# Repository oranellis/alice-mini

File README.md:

# OPA Alice Mini

Circuit from the OPA Alice design by DJJules, which itself was based on the Alice microphone by Scott Helmke, this is a PCB designed for a 3D printed mic enclosure for the JLI-2555B Capsule. I started the project off the back of the DIYPerks video where Matthew made a gorgeous mic based on the same capsule, however I wanted to connect it to my Scarlet Focusrite Solo instead and stumbled on the Alice mic. 

## Design

The circuit is identical to the OPA Alice preamp circuit with the exception of using MLCC's instead of Aluminium electrolytic capacitors. It is designed in Kicad 8 with the JLCPCB [plugin](https://github.com/Bouni/kicad-jlcpcb-tools), and ordered pre-assembled from JLCPCB. This is my first PCB design so please scrutinise it thoroughly before using or ordering one for yourself. **THE BOARD HAS NOT ARRIVED FOR ME YET AND MAY HAVE ISSUES**, please wait until I update this with the information of whether it works or not. If it does work, I will design the 3D printed enclosure and add those files here (or a link to the onshape page).

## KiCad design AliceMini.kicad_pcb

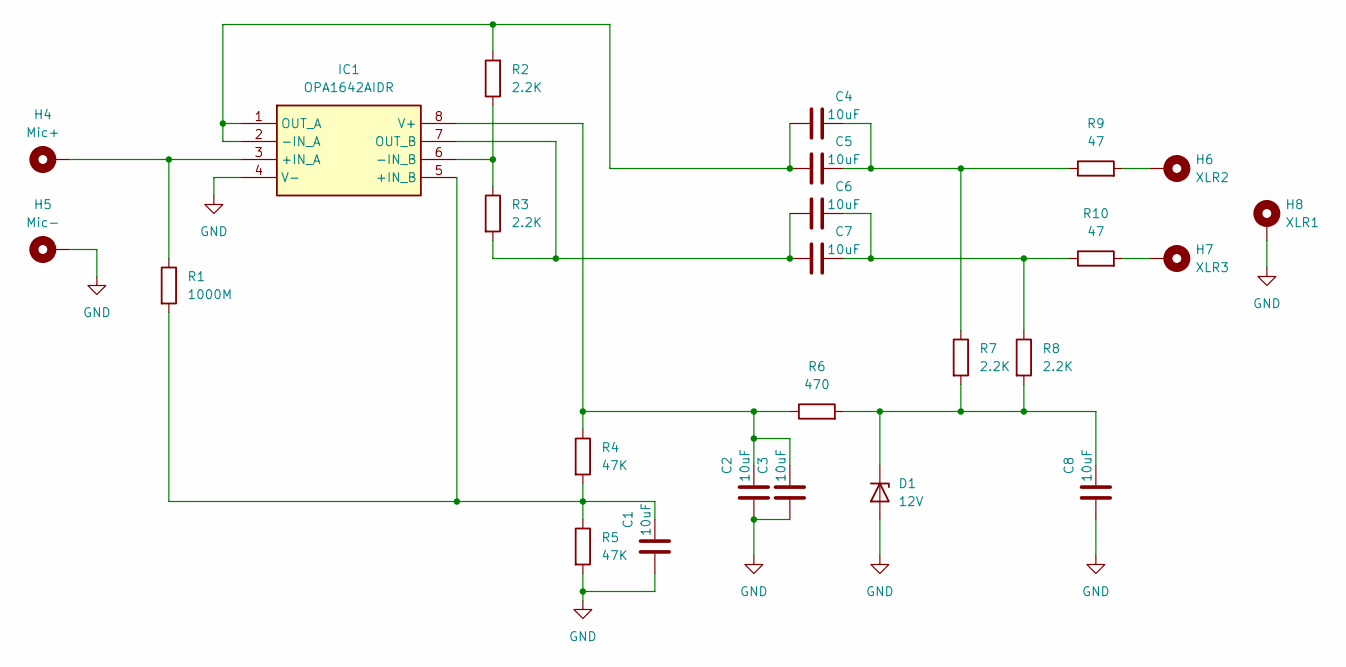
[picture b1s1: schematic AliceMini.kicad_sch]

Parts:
C1, C2, C3, C4, C5, C6, C7, C8: 10uF; C_1206_3216Metric
D1: 12V; D_SOD-123
H4: Mic+; TestPoint_THTPad_2.0x2.0mm_Drill1.0mm
H5: Mic-; TestPoint_THTPad_2.0x2.0mm_Drill1.0mm
H6: XLR2; TestPoint_THTPad_2.0x2.0mm_Drill1.0mm
H7: XLR3; TestPoint_THTPad_2.0x2.0mm_Drill1.0mm
H8: XLR1; TestPoint_THTPad_2.0x2.0mm_Drill1.0mm
IC1: OPA1642AIDR; SOIC127P600X175-8N; Mouser Part Number 595-OPA1642AIDR
R1: 1000M; R_0805_2012Metric
R2, R3, R7, R8: 2.2K; R_0603_1608Metric
R4, R5: 47K; R_0603_1608Metric
R6: 470; R_0603_1608Metric
R9, R10: 47; R_0603_1608Metric

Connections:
GND: C1.1, C2.1, C3.1, C8.1, D1.2 (A), H5.1, H8.1, IC1.4 (V-), R5.2
unnamed: C4.2, C5.2, R7.1, R9.1
unnamed: C6.2, C7.2, R8.1, R10.1
unnamed: C8.2, D1.1 (K), R6.2, R7.2, R8.2
unnamed: H6.1, R9.2
unnamed: H7.1, R10.2
unnamed: H4.1, IC1.3 (+IN_A), R1.1
unnamed: C1.2, IC1.5 (+IN_B), R1.2, R4.2, R5.1
unnamed: C4.1, C5.1, IC1.1 (OUT_A), IC1.2 (-IN_A), R2.2
unnamed: IC1.6 (-IN_B), R2.1, R3.1
unnamed: C6.1, C7.1, IC1.7 (OUT_B), R3.2
unnamed: C2.2, C3.2, IC1.8 (V+), R4.1, R6.1

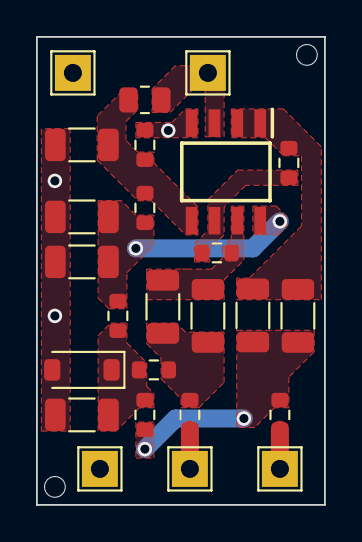
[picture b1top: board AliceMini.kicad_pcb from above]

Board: 2 copper layers, 16.0 x 26.0 mm, 25 parts (0 on the bottom side), 12 nets.

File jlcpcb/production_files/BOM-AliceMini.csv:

Comment,Designator,Footprint,LCSC,Quantity
10uF,"C1,C2,C3,C4,C5,C6,C7,C8",C_1206_3216Metric,C13585,8
12V,D1,D_SOD-123,C173429,1
470,R6,R_0603_1608Metric,C23179,1
47,"R10,R9",R_0603_1608Metric,C23182,2
47K,"R4,R5",R_0603_1608Metric,C25819,2
1000M,R1,R_0805_2012Metric,C4180315,1
2.2K,"R2,R3,R7,R8",R_0603_1608Metric,C4190,4
OPA1642AIDR,IC1,SOIC127P600X175-8N,C67640,1

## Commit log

2024-11-13 Add readme
2024-11-13 Add gitignore and remove backups
2024-11-13 Reduce board size and snap to mm instead of mils
2024-11-13 Move PCB to origin
2024-11-22 fix: Updated high impedance resistor to 1G again
2024-11-22 fix: Remove R1 silkscreen
2024-11-22 fix: Correct bad opamp rotation in prod files
